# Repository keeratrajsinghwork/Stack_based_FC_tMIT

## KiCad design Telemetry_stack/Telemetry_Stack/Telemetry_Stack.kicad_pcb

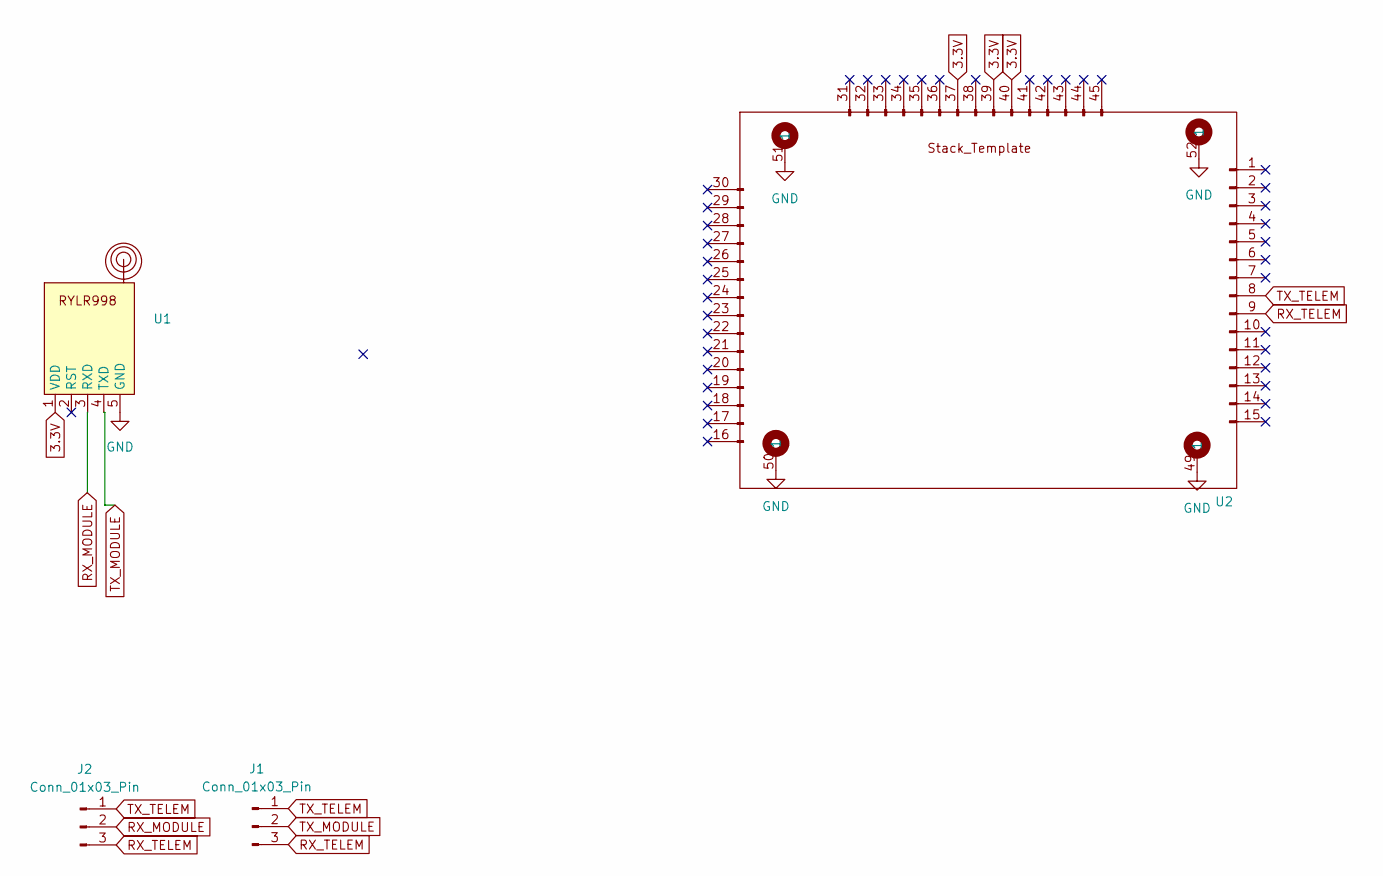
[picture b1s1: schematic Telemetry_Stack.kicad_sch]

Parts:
J1, J2: Conn_01x03_Pin; PinHeader_1x03_P2.54mm_Vertical
U1: RYLR998
U2: FC_Stack_template

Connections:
3.3V: U1.1 (VDD), U2.37, U2.39, U2.40
GND: U1.5 (GND), U2.49 (1), U2.50 (1), U2.51 (1), U2.52 (1)
RX_MODULE: J2.2, U1.3 (RXD)
RX_TELEM: J1.3, J2.3, U2.9
TX_MODULE: J1.2, U1.4 (TXD)
TX_TELEM: J1.1, J2.1, U2.8

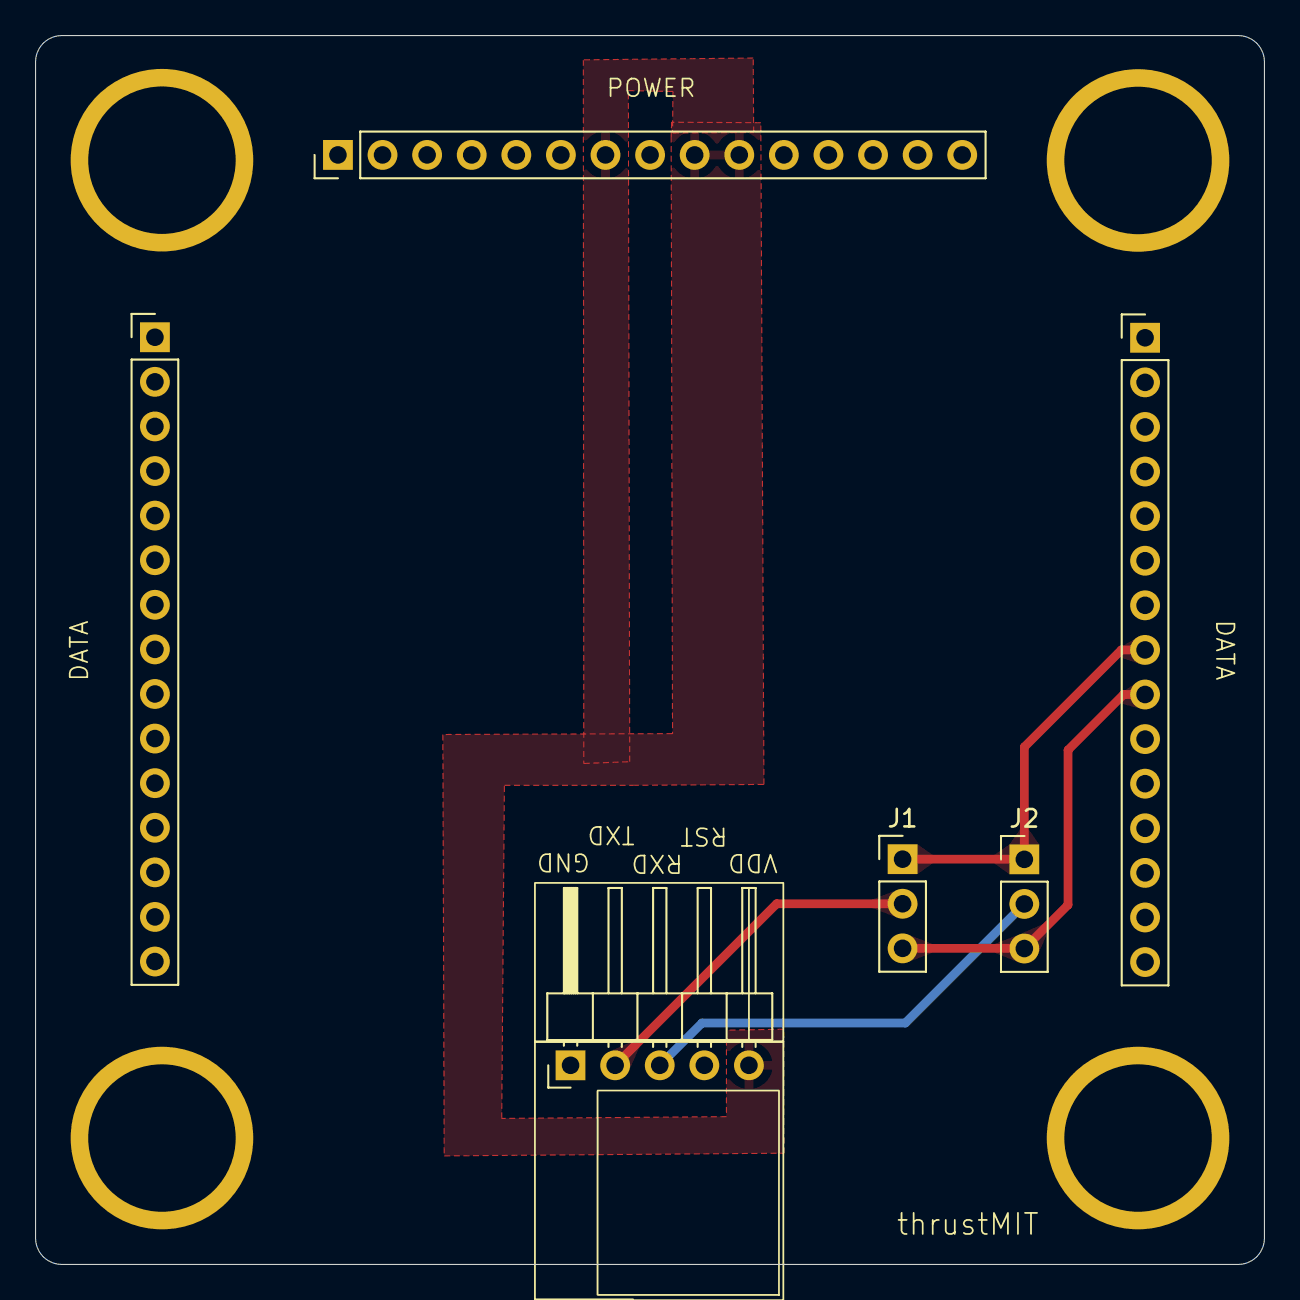
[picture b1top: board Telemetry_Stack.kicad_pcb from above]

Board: 2 copper layers, 70.0 x 70.0 mm, 4 parts (0 on the bottom side), 6 nets.

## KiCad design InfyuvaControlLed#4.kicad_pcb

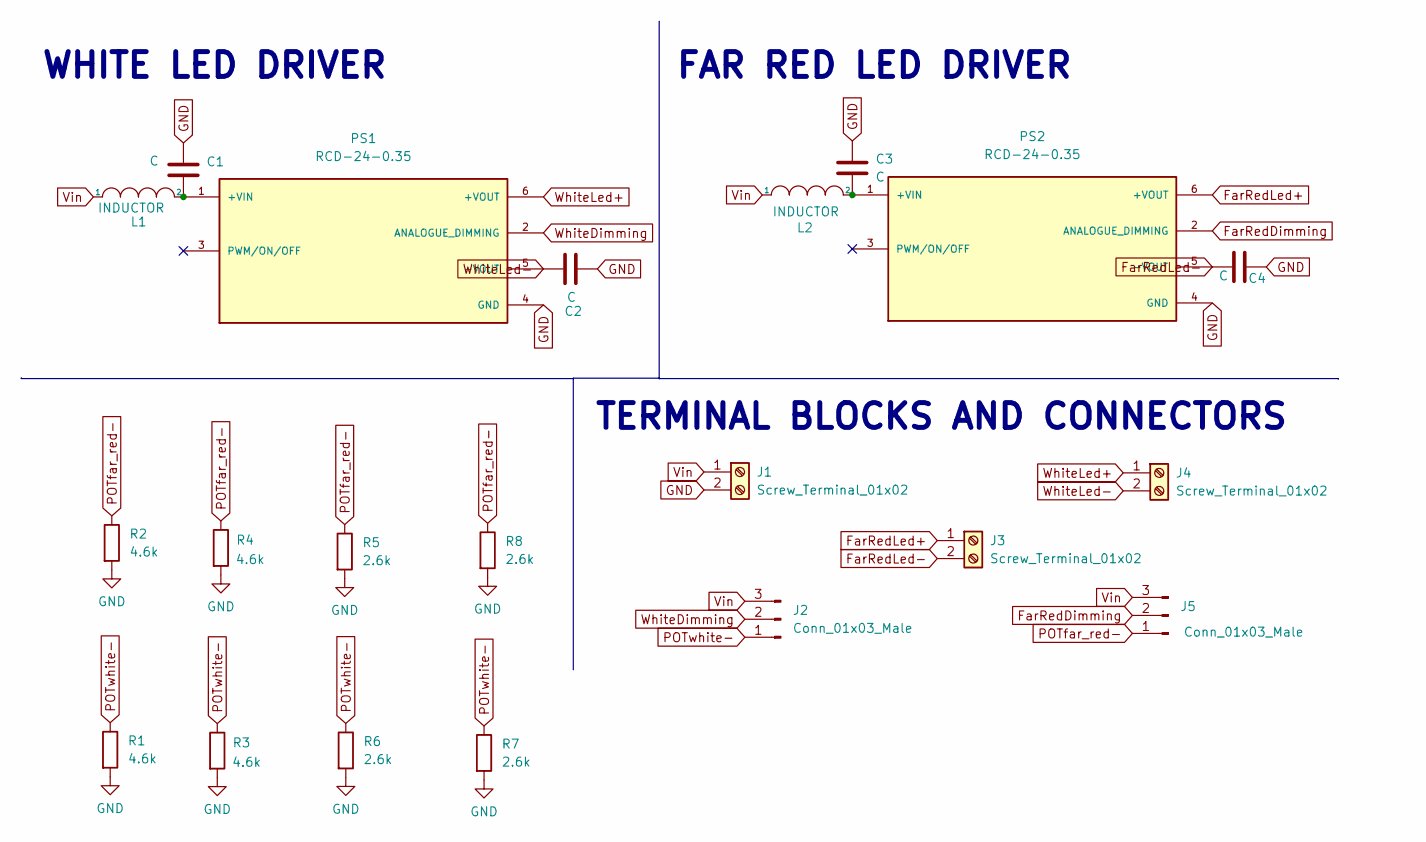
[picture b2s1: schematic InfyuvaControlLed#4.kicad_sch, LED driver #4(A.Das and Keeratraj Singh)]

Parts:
C1, C2, C3, C4: C; C_1206_3216Metric
J1, J3, J4: Screw_Terminal_01x02; TerminalBlock_bornier-2_P5.08mm
J2, J5: Conn_01x03_Male; FanPinHeader_1x03_P2.54mm_Vertical
L1, L2: INDUCTOR; IND_BOURNS_SRR1208
PS1, PS2: RCD-24-0.35; CONV_RCD-24-0.35; PARTREV 1
R1, R2, R3, R4: 4.6k; R_1206_3216Metric
R5, R6, R7, R8: 2.6k; R_1206_3216Metric

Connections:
FarRedDimming: J5.2, PS2.2 (ANALOGUE_DIMMING)
FarRedLed+: J3.1, PS2.6 (+VOUT)
FarRedLed-: C4.1, J3.2, PS2.5 (-VOUT)
GND: C1.2, C2.2, C3.2, C4.2, J1.2, PS1.4 (GND), PS2.4 (GND), R1.2, R2.2, R3.2, R4.2, R5.2, R6.2, R7.2, R8.2
unnamed: C1.1, L1.2, PS1.1 (+VIN)
unnamed: C3.1, L2.2, PS2.1 (+VIN)
POTfar_red-: J5.1, R2.1, R4.1, R5.1, R8.1
POTwhite-: J2.1, R1.1, R3.1, R6.1, R7.1
Vin: J1.1, J2.3, J5.3, L1.1, L2.1
WhiteDimming: J2.2, PS1.2 (ANALOGUE_DIMMING)
WhiteLed+: J4.1, PS1.6 (+VOUT)
WhiteLed-: C2.1, J4.2, PS1.5 (-VOUT)

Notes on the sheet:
FAR RED LED DRIVER
WHITE LED DRIVER
TERMINAL BLOCKS AND CONNECTORS

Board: 2 copper layers, 21 parts (1 on the bottom side), 12 nets, no tracks yet.

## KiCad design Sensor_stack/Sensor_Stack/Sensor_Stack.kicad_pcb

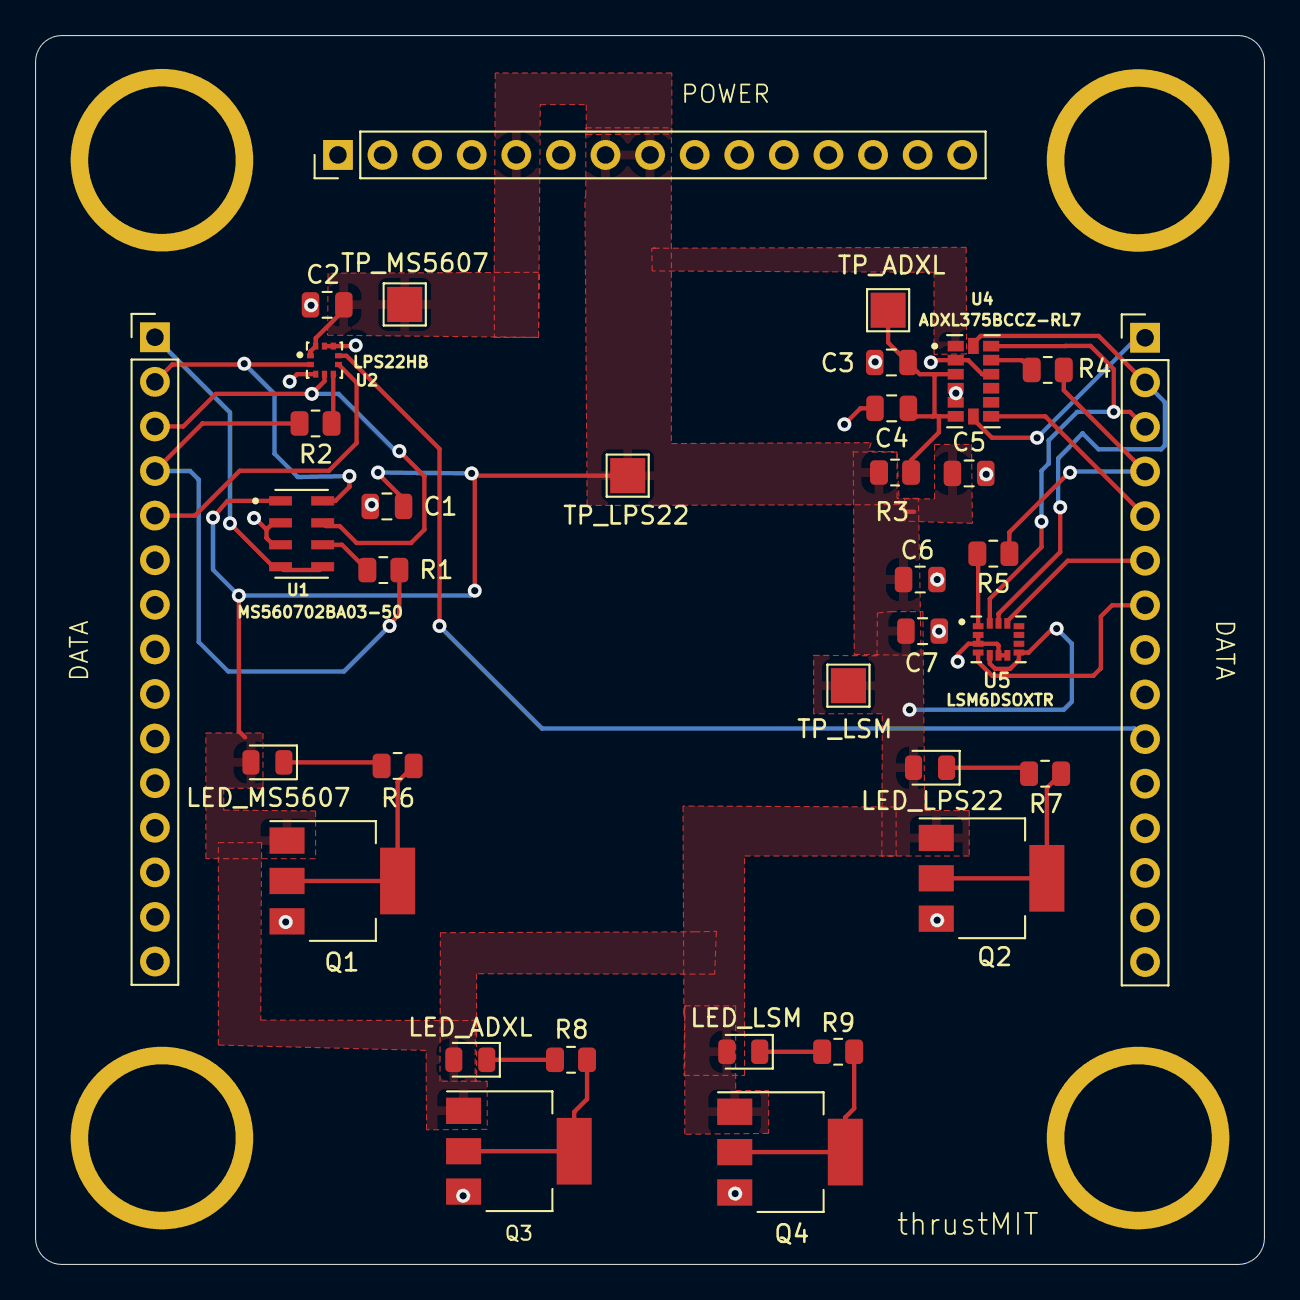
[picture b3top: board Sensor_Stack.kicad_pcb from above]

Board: 2 copper layers, 70.0 x 70.0 mm, 33 parts (0 on the bottom side), 28 nets.

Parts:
C1, C2, C4, C5, C6, C7: 0.1u; C_0805_2012Metric
C3: 10u; C_0805_2012Metric
LED_ADXL: LED_IMU; LED_0805_2012Metric
LED_LPS22: LED_IMU; LED_0805_2012Metric
LED_LSM: LED_IMU; LED_0805_2012Metric
LED_MS5607: LED_IMU; LED_0805_2012Metric
Q1, Q2, Q3, Q4: PZT2222A; SOT-223-3_TabPin2
R1, R2, R4, R5: 22; R_0805_2012Metric
R3: 100; R_0805_2012Metric
R6, R7, R8, R9: 56; R_0805_2012Metric
TP_ADXL: TestPoint_Probe; TestPoint_Pad_2.0x2.0mm
TP_LPS22: TestPoint_Probe; TestPoint_Pad_2.0x2.0mm
TP_LSM: TestPoint_Probe; TestPoint_Pad_2.0x2.0mm
TP_MS5607: TestPoint_Probe; TestPoint_Pad_2.0x2.0mm
U1: MS560702BA03-50
U2: LPS22HB
U4: ADXL375BCCZ-RL7
U5: LSM6DSOXTR
U6: FC_Stack_template

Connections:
3.3V: C1.1, C2.1, C5.1, C6.2, C7.1, LED_ADXL.2 (A), LED_LPS22.2 (A), LED_LSM.2 (A), LED_MS5607.2 (A), Q1.1 (B), Q2.1 (B), Q3.1 (B), Q4.1 (B), R3.1, TP_LPS22.1, TP_LSM.1, TP_MS5607.1, U1.1 (VDD), U2.1 (VDD_IO), U2.10 (VDD), U4.1 (Vdd/io), U5.5 (VDDIO), U5.8 (VDD), U6.35, U6.37, U6.38
CS_ADXL: U4.7 (CS), U6.1
CS_LPS: U2.6 (CS), U6.26
CS_LSM: U5.12 (CS), U6.6
CS_MS5607: U1.4 (~CSB), U1.5 (~CSB), U6.30
GND: C1.2, C2.2, C3.2, C4.2, C5.2, C6.1, C7.2, Q1.3 (E), Q2.3 (E), Q3.3 (E), Q4.3 (E), U1.2 (PS), U1.3 (GND), U2.3 (RES), U2.8 (GND), U2.9 (GND), U4.2 (GND), U4.4 (GND), U4.5 (GND), U4.11 (Reserved), U5.2 (SDX), U5.3 (SCX), U5.6 (GND), U5.7 (GND), U6.49 (1), U6.50 (1), U6.51 (1), U6.52 (1)
INT_ADXL: U4.8 (INT1), U6.5
INT_LPS: U2.7 (INT_DRDY), U6.10
INT_LSM: U5.4 (INT1), U6.7
MISO_SPI1: R1.2, R2.1, U6.27
MISO_SPI2: R4.2, R5.1, U6.4
MOSI_SPI1: U1.7 (SDI/SDA), U2.4 (SDA/SDI/SDO), U6.28
MOSI_SPI2: U4.13 (SDA/SDI/SDIO), U5.14 (SDA), U6.3
unnamed: LED_MS5607.1 (K), R6.1
unnamed: LED_LPS22.1 (K), R7.1
unnamed: LED_ADXL.1 (K), R8.1
unnamed: LED_LSM.1 (K), R9.1
unnamed: Q1.2 (C), R6.2
unnamed: Q2.2 (C), R7.2
unnamed: Q3.2 (C), R8.2
unnamed: Q4.2 (C), R9.2
unnamed: R1.1, U1.6 (SDO)
unnamed: R2.2, U2.5 (SDO/SA0)
unnamed: R4.1, U4.12 (SDO)
unnamed: C3.1, C4.1, R3.2, TP_ADXL.1, U4.3 (Reserved), U4.6 (Vs)
unnamed: R5.2, U5.1 (SDO/SA0)
SCLK_SPI1: U1.8 (SCLK), U2.2 (SCL/SPC), U6.29
SCLK_SPI2: U4.14 (SCL/SCLK), U5.13 (SCL), U6.2

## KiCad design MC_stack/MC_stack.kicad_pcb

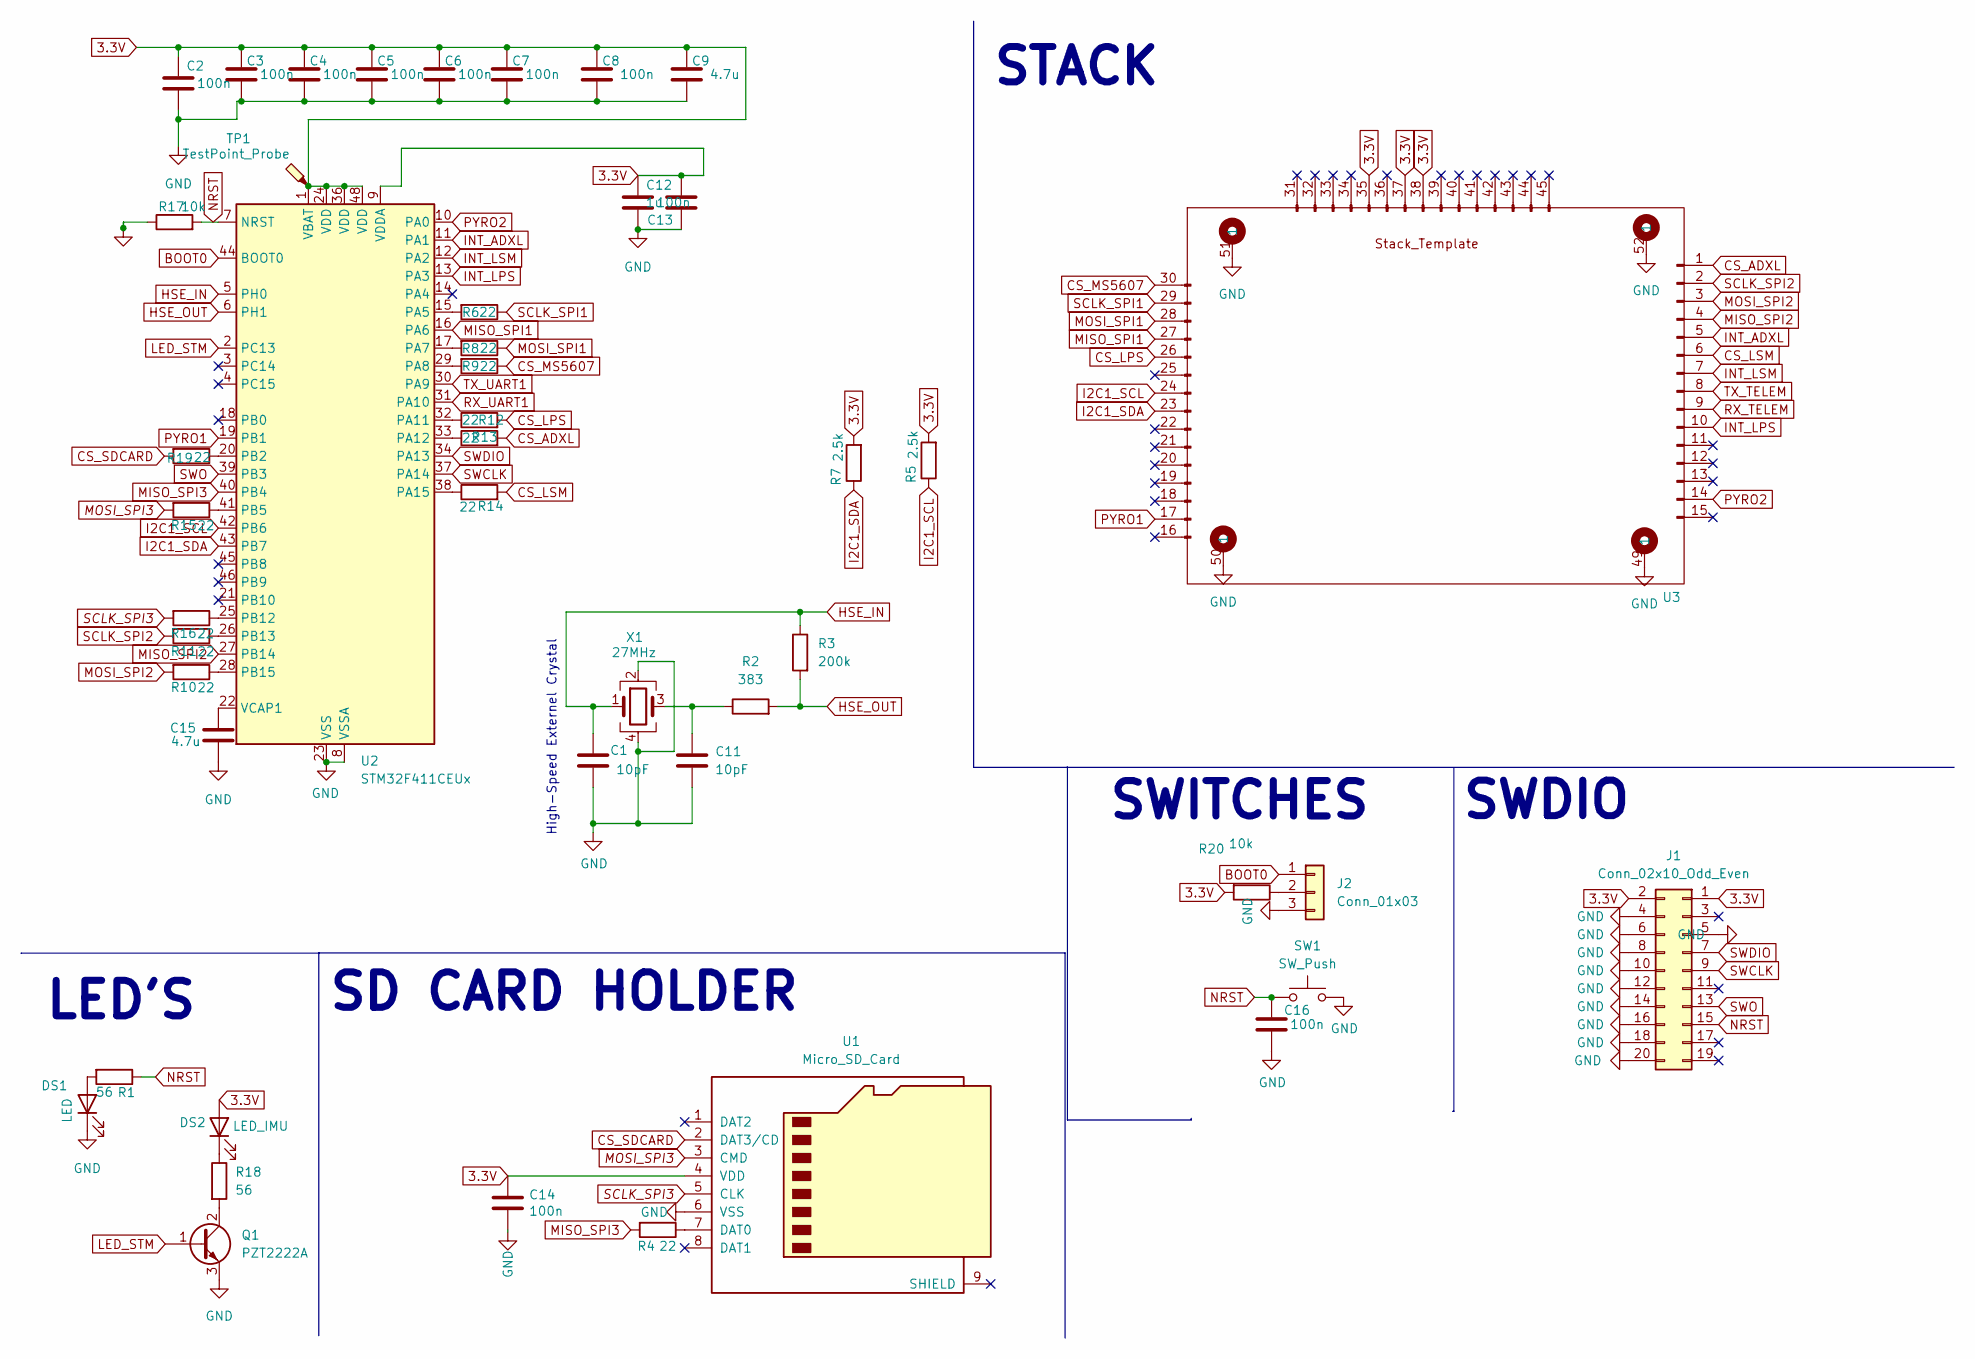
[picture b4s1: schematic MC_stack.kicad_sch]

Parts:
C1, C11: 10pF; C_0805_2012Metric
C2, C3, C4, C5, C6, C7, C8, C12, C14, C16: 100n; C_0805_2012Metric
C9, C15: 4.7u; C_0805_2012Metric
C13: 1u; C_0805_2012Metric
DS1: LED; LED_0805_2012Metric
DS2: LED_IMU; LED_0805_2012Metric
J1: Conn_02x10_Odd_Even; PinHeader_2x10_P2.54mm_Vertical
J2: Conn_01x03; PinHeader_1x03_P2.54mm_Vertical
Q1: PZT2222A; SOT-223-3_TabPin2
R1, R18: 56; R_0805_2012Metric
R2: 383; R_0805_2012Metric
R3: 200k; R_0805_2012Metric
R4, R6, R8, R9, R10, R11, R12, R13, R14, R15, R16, R19: 22; R_0805_2012Metric
R5, R7: 2.5k; R_0805_2012Metric
R17, R20: 10k; R_0805_2012Metric
SW1: SW_Push; SW_Push_SPST_NO_Alps_SKRK
TP1: TestPoint_Probe; TestPoint_Pad_2.0x2.0mm
U1: Micro_SD_Card; microSD_HC_Molex_104031-0811
U2: STM32F411CEUx; QFN-48-1EP_7x7mm_P0.5mm_EP5.6x5.6mm
U3: FC_Stack_template
X1: 27MHz; Crystal_SMD_Abracon_ABM8G-4Pin_3.2x2.5mm

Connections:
3.3V: C2.1, C3.1, C4.1, C5.1, C6.1, C7.1, C8.1, C9.1, C12.1, C13.2, C14.1, DS2.2 (A), J1.1, J1.2, R5.2, R7.2, R20.2, TP1.1, U1.4 (VDD), U2.1 (VBAT), U2.9 (VDDA), U2.24 (VDD), U2.36 (VDD), U2.48 (VDD), U3.35, U3.37, U3.38
BOOT0: J2.1, U2.44 (BOOT0)
CS_ADXL: R13.2, U3.1
CS_LPS: R12.2, U3.26
CS_LSM: R14.2, U3.6
CS_MS5607: R9.1, U3.30
CS_SDCARD: R19.2, U1.2 (DAT3/CD)
GND: C1.2, C2.2, C3.2, C4.2, C5.2, C6.2, C7.2, C8.2, C9.2, C11.2, C12.2, C13.1, C14.2, C15.2, C16.2, DS1.1 (K), J1.4, J1.5, J1.6, J1.8, J1.10, J1.12, J1.14, J1.16, J1.18, J1.20, J2.3, Q1.3 (E), R17.1, SW1.2, U1.6 (VSS), U2.8 (VSSA), U2.23 (VSS), U2.35 (VSS), U2.47 (VSS), U2.49 (VSS), U3.49 (1), U3.50 (1), U3.51 (1), U3.52 (1), X1.2, X1.4
HSE_IN: C1.1, R3.1, U2.5 (PH0), X1.1
HSE_OUT: R2.2, R3.2, U2.6 (PH1)
I2C1_SCL: R5.1, U2.42 (PB6), U3.24
I2C1_SDA: R7.1, U2.43 (PB7), U3.23
INT_ADXL: U2.11 (PA1), U3.5
INT_LPS: U2.13 (PA3), U3.10
INT_LSM: U2.12 (PA2), U3.7
LED_STM: Q1.1 (B), U2.2 (PC13)
MISO_SPI1: U2.16 (PA6), U3.27
MISO_SPI2: U2.27 (PB14), U3.4
MISO_SPI3: R4.2, U2.40 (PB4)
MOSI_SPI1: R8.1, U3.28
MOSI_SPI2: R10.2, U3.3
MOSI_SPI3: R15.2, U1.3 (CMD)
NRST: C16.1, J1.15, R1.1, R17.2, SW1.1, U2.7 (NRST)
unnamed: C11.1, R2.1, X1.3
unnamed: DS1.2 (A), R1.2
unnamed: DS2.1 (K), R18.1
unnamed: J2.2, R20.1
unnamed: Q1.2 (C), R18.2
unnamed: R4.1, U1.7 (DAT0)
unnamed: R6.2, U2.15 (PA5)
unnamed: R8.2, U2.17 (PA7)
unnamed: R9.2, U2.29 (PA8)
unnamed: R12.1, U2.32 (PA11)
unnamed: R13.1, U2.33 (PA12)
unnamed: R14.1, U2.38 (PA15)
unnamed: R19.1, U2.20 (PB2)
unnamed: R15.1, U2.41 (PB5)
unnamed: R16.1, U2.25 (PB12)
unnamed: R11.1, U2.26 (PB13)
unnamed: R10.1, U2.28 (PB15)
unnamed: C15.1, U2.22 (VCAP1)
RX_TELEM: U3.9
RX_UART1: U2.31 (PA10)
SCLK_SPI1: R6.1, U3.29
SCLK_SPI2: R11.2, U3.2
SCLK_SPI3: R16.2, U1.5 (CLK)
SWCLK: J1.9, U2.37 (PA14)
SWDIO: J1.7, U2.34 (PA13)
SWO: J1.13, U2.39 (PB3)
TX_TELEM: U3.8
TX_UART1: U2.30 (PA9)

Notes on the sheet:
SWDIO
LED'S
High-Speed Externel Crystal
SD CARD HOLDER
STACK
SWITCHES

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
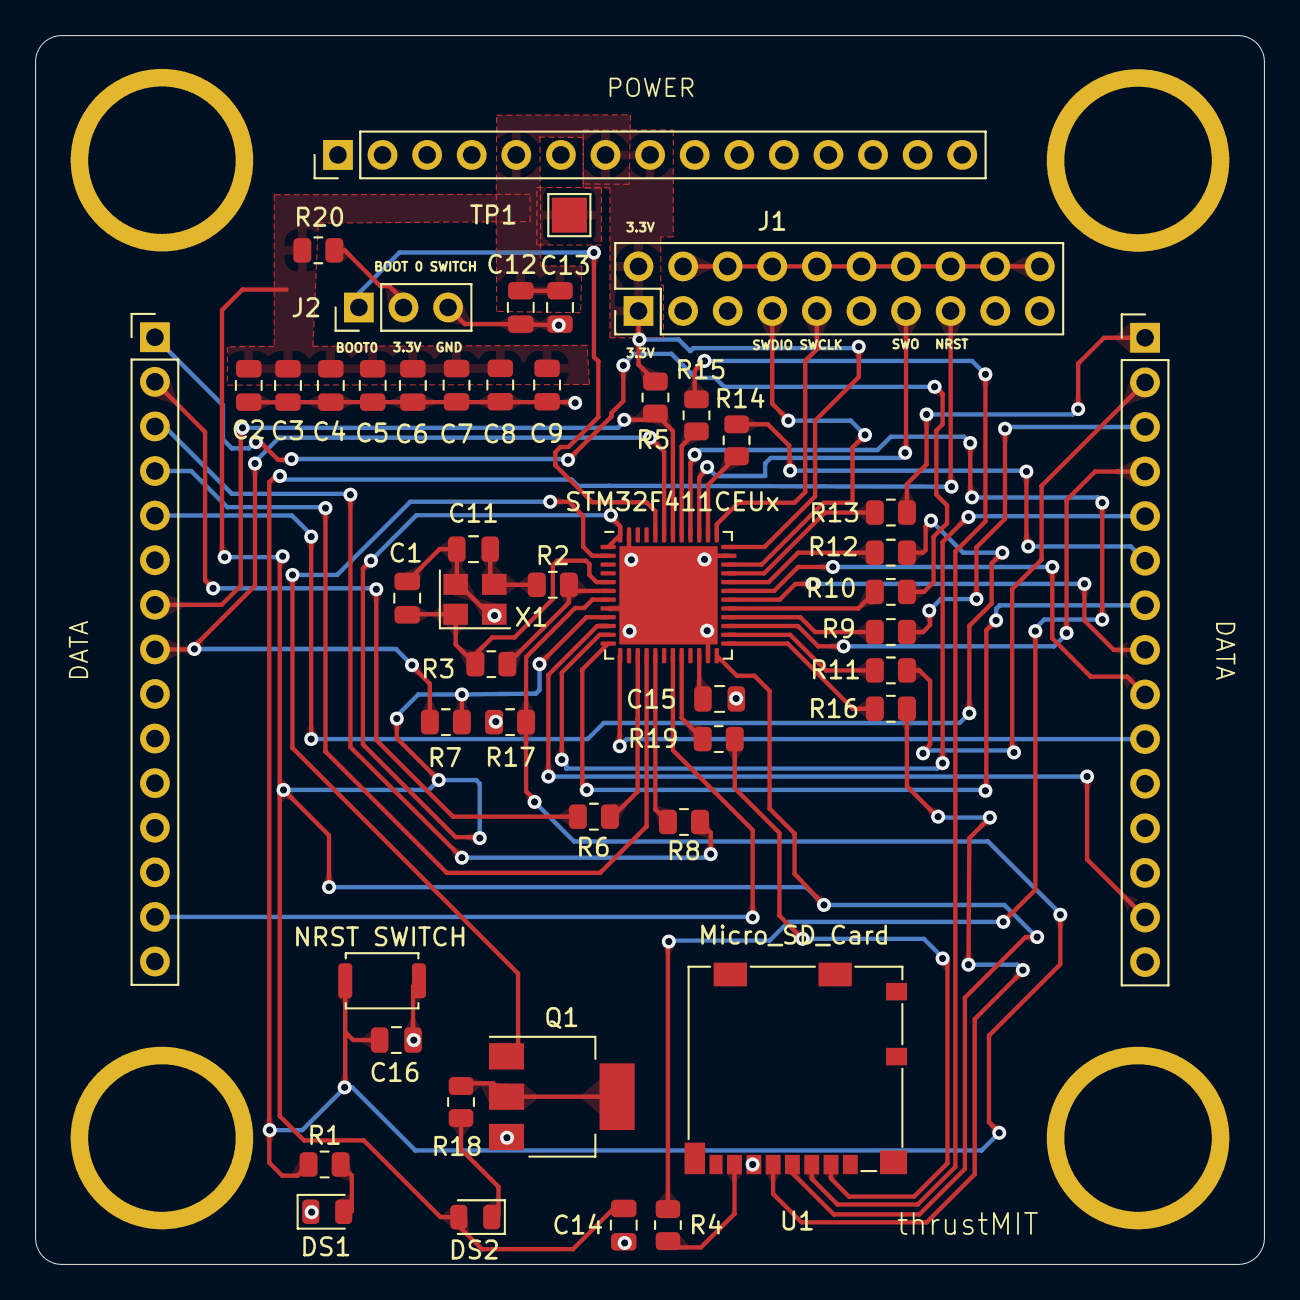
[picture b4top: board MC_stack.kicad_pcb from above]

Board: 2 copper layers, 70.0 x 70.0 mm, 46 parts (0 on the bottom side), 47 nets.

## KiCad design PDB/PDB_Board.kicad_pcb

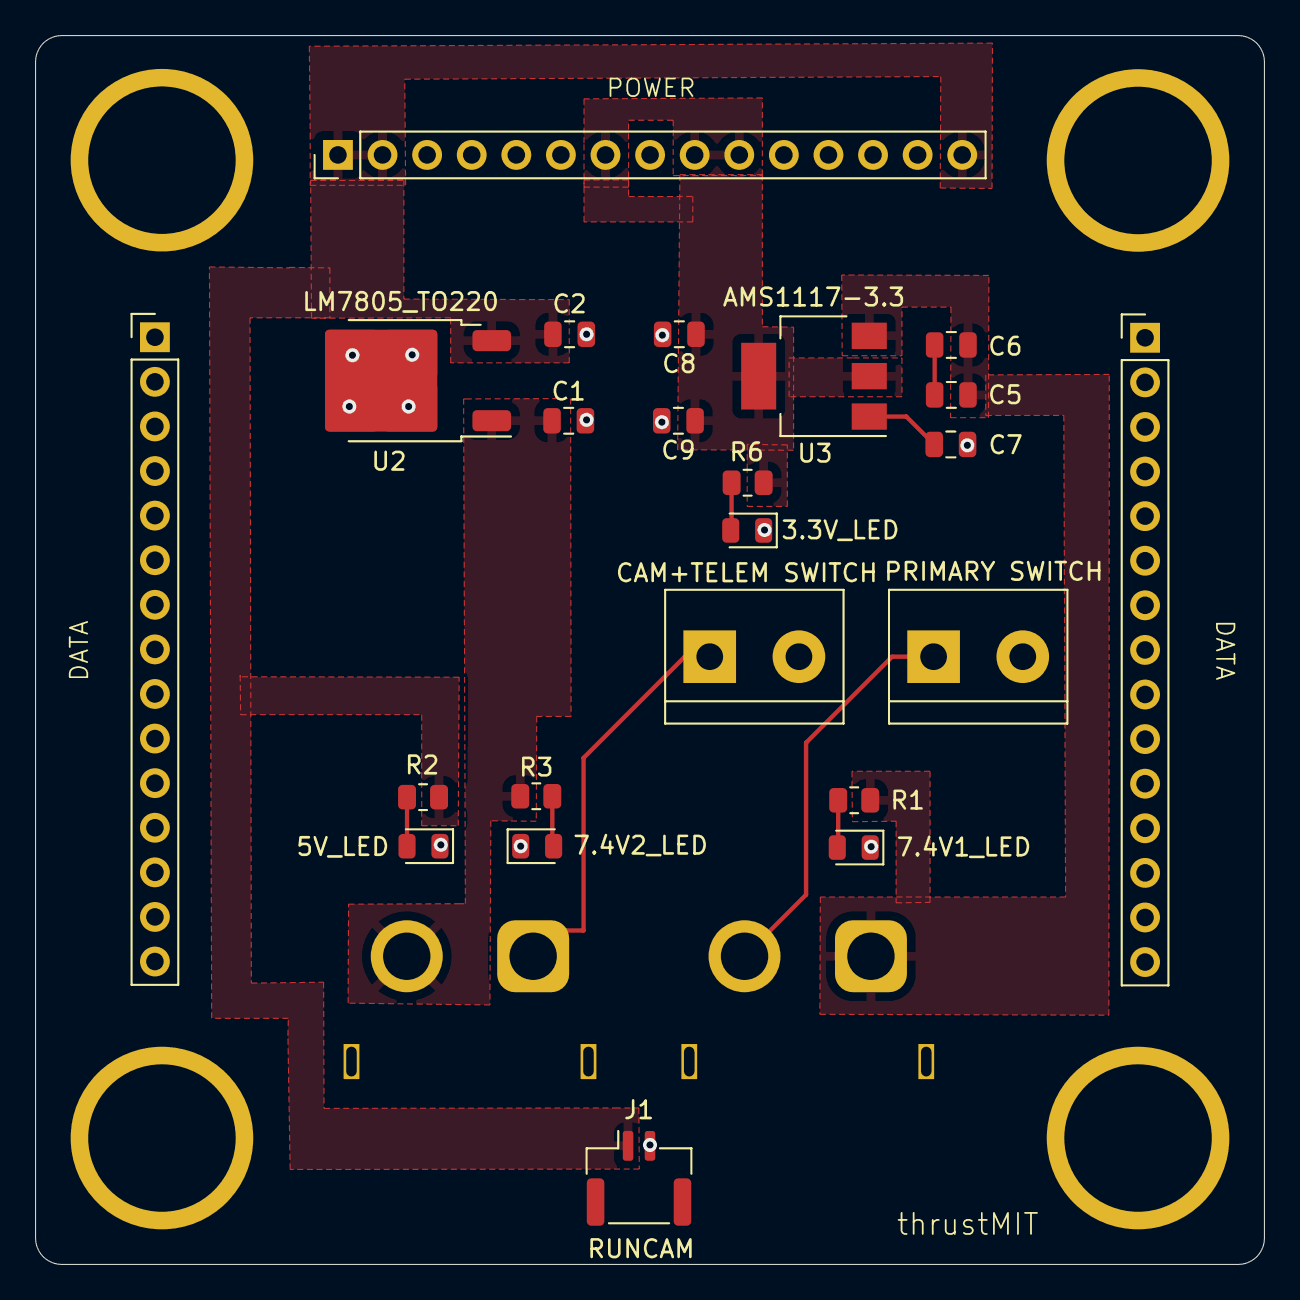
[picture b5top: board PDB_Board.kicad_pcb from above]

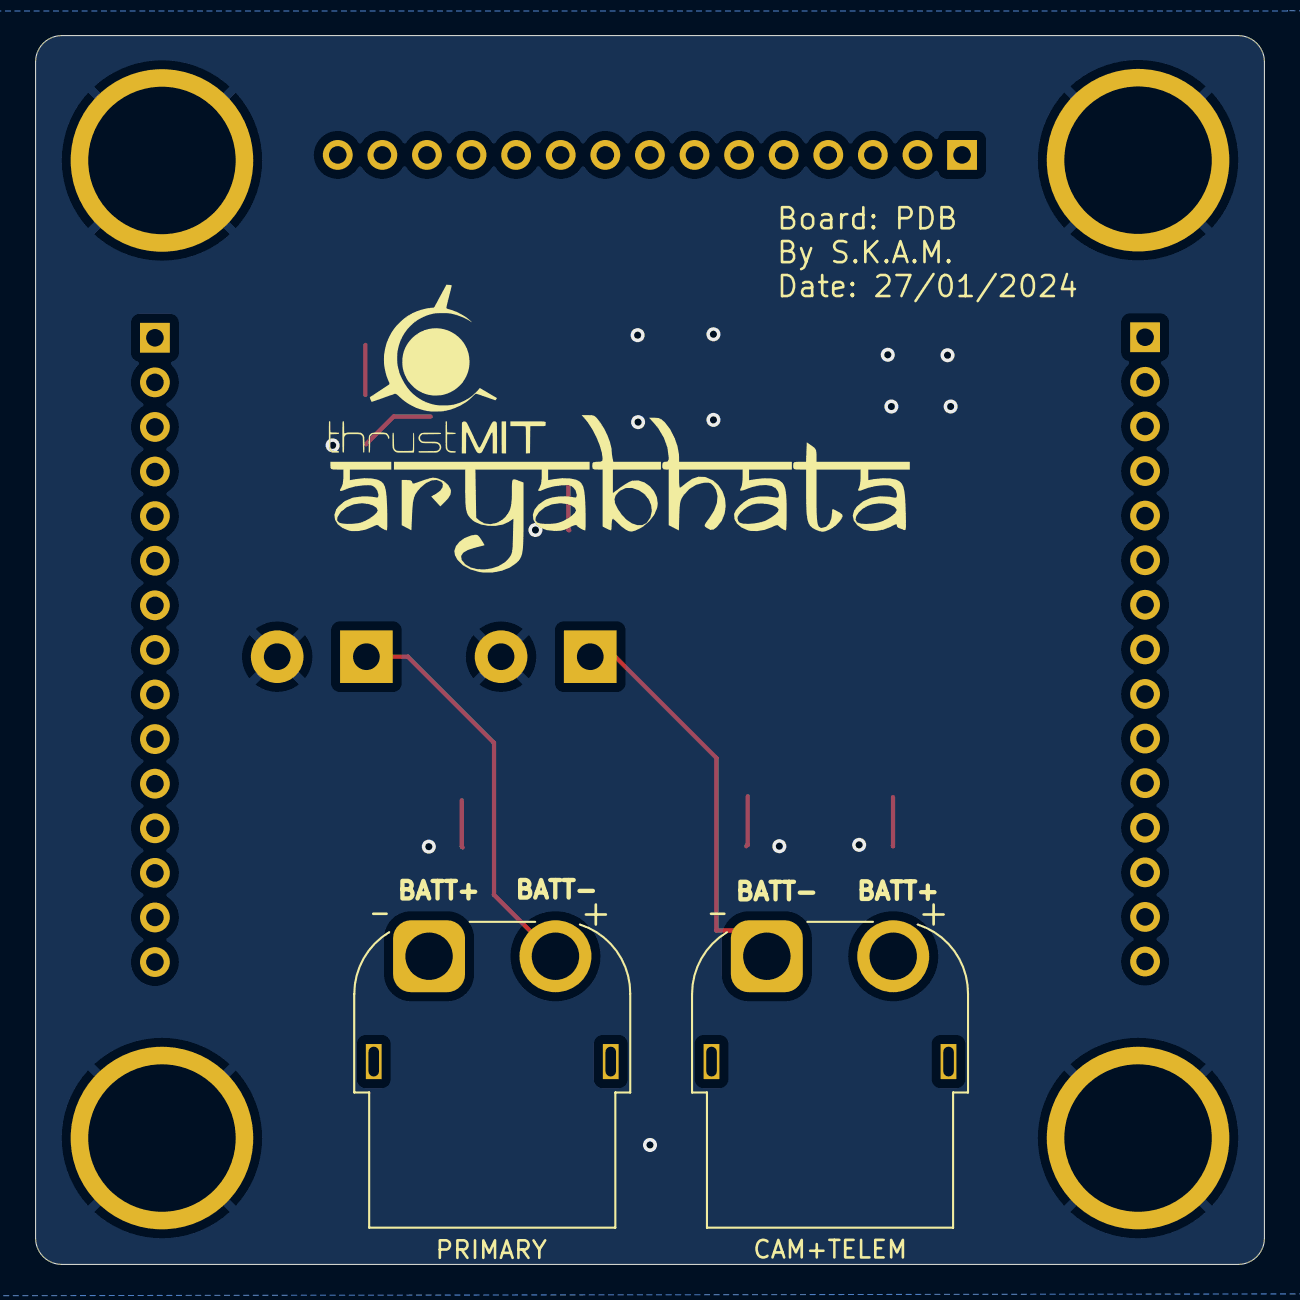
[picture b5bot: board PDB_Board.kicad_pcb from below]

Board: 2 copper layers, 70.0 x 70.0 mm, 23 parts (2 on the bottom side), 13 nets.

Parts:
3.3V_LED, 5V_LED, 7.4V1_LED, 7.4V2_LED: LED; LED_0805_2012Metric
C1: 0.33u; C_0805_2012Metric
C2: 0.1u; C_0805_2012Metric
C5, C8: 10u; C_0805_2012Metric
C6, C7, C9: 100nF; C_0805_2012Metric
CAM+TELEM: Conn_01x02_Pin; AMASS_XT60PW-F_1x02_P7.20mm_Horizontal
CAM+TELEM SWITCH: Screw_Terminal_01x02; TerminalBlock_bornier-2_P5.08mm
J1: Conn_01x02_Pin; JST_GH_SM02B-GHS-TB_1x02-1MP_P1.25mm_Horizontal
PRIMARY: Conn_01x02_Pin; AMASS_XT60PW-F_1x02_P7.20mm_Horizontal
PRIMARY SWITCH: Screw_Terminal_01x02; TerminalBlock_bornier-2_P5.08mm
R1, R2, R3: 220; R_0805_2012Metric
R6: 56; R_0805_2012Metric
U1: FC_stack; FC_Stack_template
U2: LM7805_TO220; TO-252-2
U3: AMS1117-3.3; SOT-223-3_TabPin2

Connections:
3.3V: C8.1, C9.1, R6.1, U1.37, U1.39, U1.40, U3.2 (VO)
5V: C2.1, J1.1, R2.1, U1.31, U1.32, U1.45, U2.3 (VO)
7.4V1: C5.1, C6.1, PRIMARY.1, R1.1, U3.3 (VI)
7.4V1_SWITCH: PRIMARY.2, PRIMARY SWITCH.1
7.4V2: C1.1, CAM+TELEM.2, R3.1, U2.1 (VI)
7.4V2_SWITCH: CAM+TELEM.1, CAM+TELEM SWITCH.1
GND: 3.3V_LED.1 (K), 5V_LED.1 (K), 7.4V1_LED.1 (K), 7.4V2_LED.1 (K), C1.2, C2.2, C7.2, C8.2, C9.2, CAM+TELEM SWITCH.2, J1.2, PRIMARY SWITCH.2, U1.49 (1), U1.50 (1), U1.51 (1), U1.52 (1), U2.2 (GND)
unnamed: C5.2, C6.2
unnamed: 7.4V1_LED.2 (A), R1.2
unnamed: 5V_LED.2 (A), R2.2
unnamed: 7.4V2_LED.2 (A), R3.2
unnamed: 3.3V_LED.2 (A), R6.2
unnamed: C7.1, U3.1 (GND)

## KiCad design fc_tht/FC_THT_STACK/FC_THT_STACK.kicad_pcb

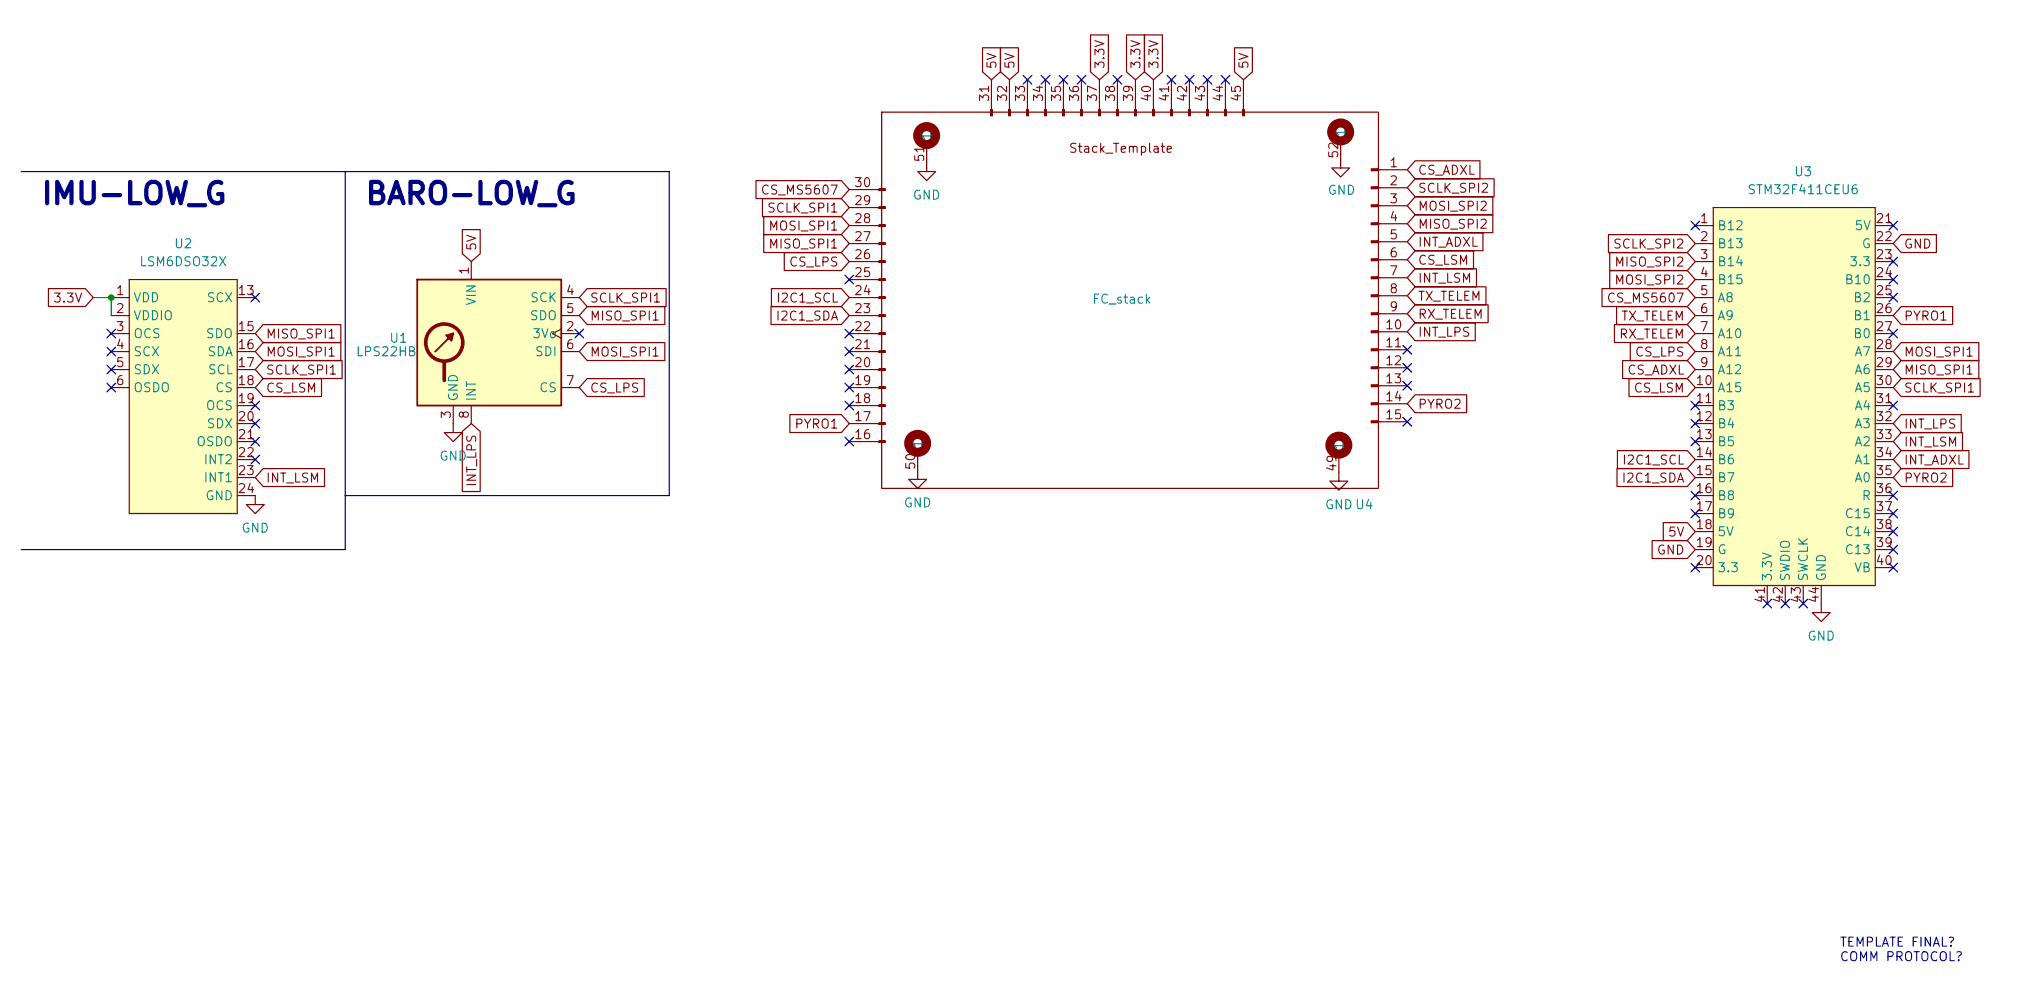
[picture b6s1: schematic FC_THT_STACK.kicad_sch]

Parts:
U1: LPS22HB; LPS22HB_ThrustMIT
U2: LSM6DSO32X
U3: STM32F411CEU6
U4: FC_stack; FC_Stack_template

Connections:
3.3V: U2.1 (VDD), U2.2 (VDDIO), U4.37, U4.39, U4.40
5V: U1.1 (VIN), U3.18 (5V), U4.31, U4.32, U4.45
CS_ADXL: U3.9 (A12), U4.1
CS_LPS: U1.7 (CS), U3.8 (A11), U4.26
CS_LSM: U2.18 (CS), U3.10 (A15), U4.6
CS_MS5607: U3.5 (A8), U4.30
GND: U1.3 (GND), U2.24 (GND), U3.19 (G), U3.22 (G), U3.44 (GND), U4.49 (1), U4.50 (1), U4.51 (1), U4.52 (1)
I2C1_SCL: U3.14 (B6), U4.24
I2C1_SDA: U3.15 (B7), U4.23
INT_ADXL: U3.34 (A1), U4.5
INT_LPS: U1.8 (INT), U3.32 (A3), U4.10
INT_LSM: U2.23 (INT1), U3.33 (A2), U4.7
MISO_SPI1: U1.5 (SDO), U2.15 (SDO), U3.29 (A6), U4.27
MISO_SPI2: U3.3 (B14), U4.4
MOSI_SPI1: U1.6 (SDI), U2.16 (SDA), U3.28 (A7), U4.28
MOSI_SPI2: U3.4 (B15), U4.3
PYRO1: U3.26 (B1), U4.17
PYRO2: U3.35 (A0), U4.14
RX_TELEM: U3.7 (A10), U4.9
SCLK_SPI1: U1.4 (SCK), U2.17 (SCL), U3.30 (A5), U4.29
SCLK_SPI2: U3.2 (B13), U4.2
TX_TELEM: U3.6 (A9), U4.8

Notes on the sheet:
TEMPLATE FINAL? COMM PROTOCOL?
BARO-LOW_G
IMU-LOW_G

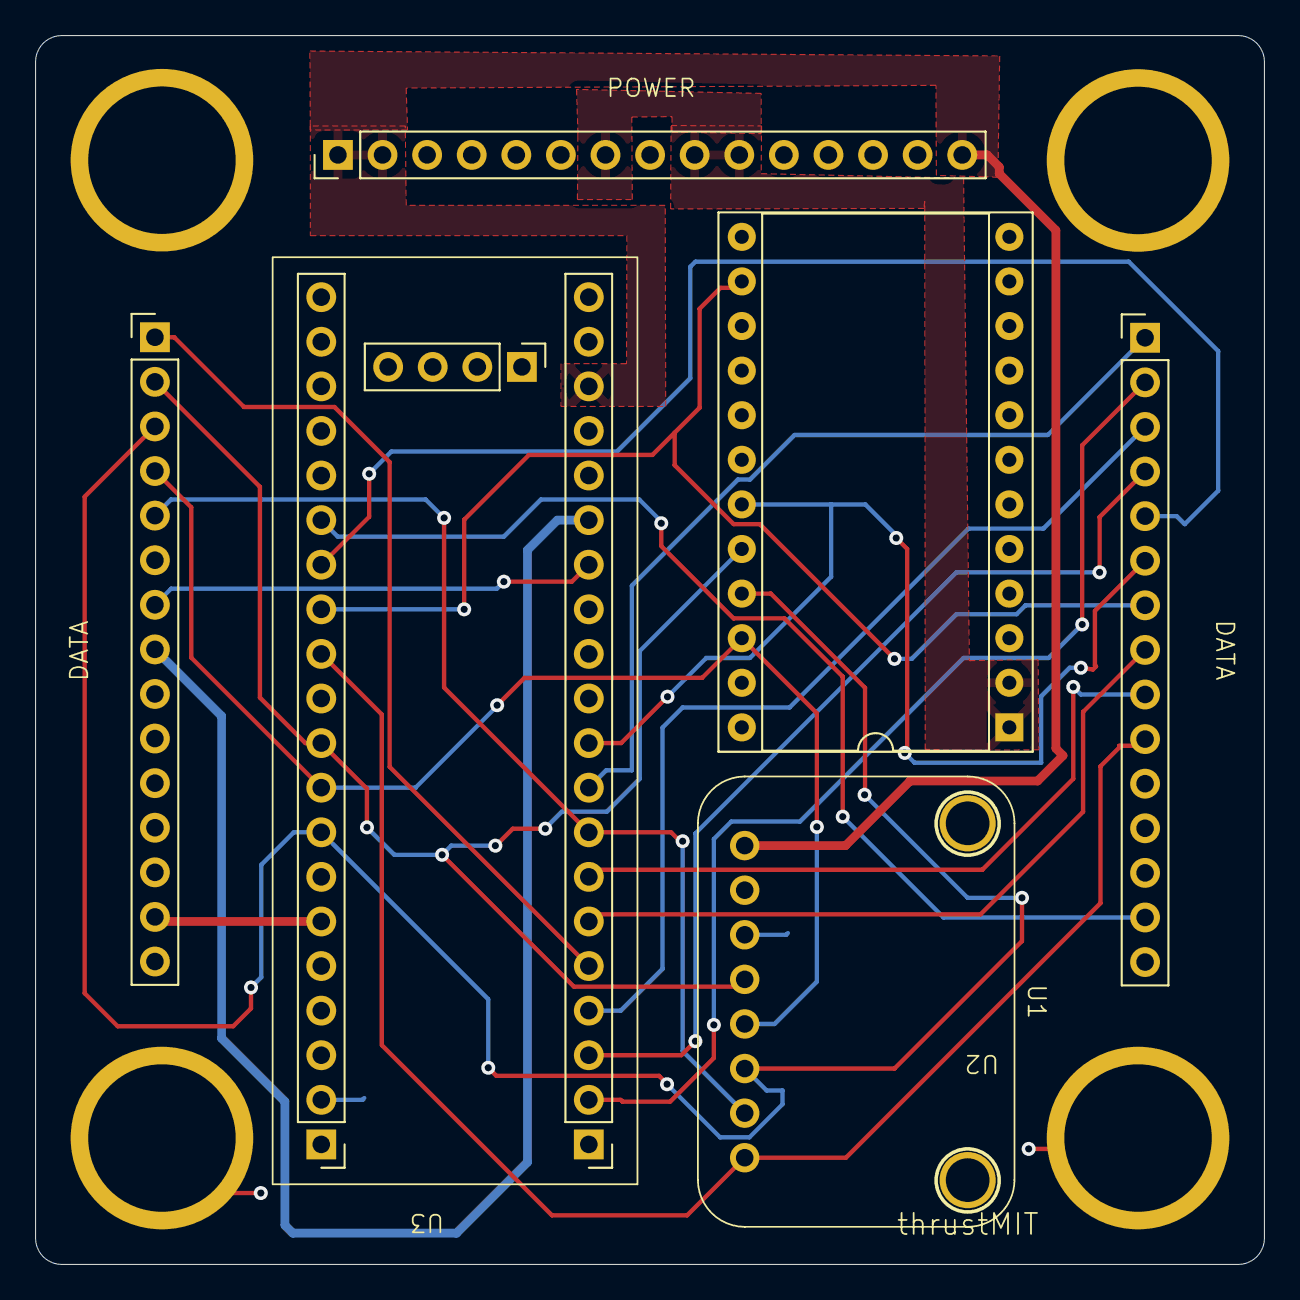
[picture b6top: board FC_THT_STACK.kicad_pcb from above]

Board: 2 copper layers, 70.0 x 70.0 mm, 4 parts (0 on the bottom side), 22 nets.
